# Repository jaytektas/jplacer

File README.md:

# jplacer

Pick-and-place machine control, built on JFramework.

## Building

Needs the JFramework SDK installed at `$HOME/jframework-sdk`, plus CMake, Ninja and OpenSSL.

    cmake -S . -B build -G Ninja -DCMAKE_PREFIX_PATH=$HOME/jframework-sdk
    cmake --build build
    ./build/jplacer

## Releases

Linux releases are AppImages that update themselves: jplacer checks for a newer release when it opens
and from Help > Check For Updates…. Edit > Preferences turns the startup check off and on, and opts in
to beta versions.

## License

GPL-3.0-or-later. See [LICENSE](LICENSE).

## Credits

jplacer follows [OpenPnP](https://openpnp.org) and carries some of it (its icons, translations, default
configuration, illustrations and BlindsFeeder models), under OpenPnP's GPL-3.0-or-later: Copyright (C) Jason von
Nieda and the OpenPnP contributors. jplacer is a separate project, not made or endorsed by OpenPnP.
[NOTICE.md](NOTICE.md) says what comes from where, and the licences of what is built in.

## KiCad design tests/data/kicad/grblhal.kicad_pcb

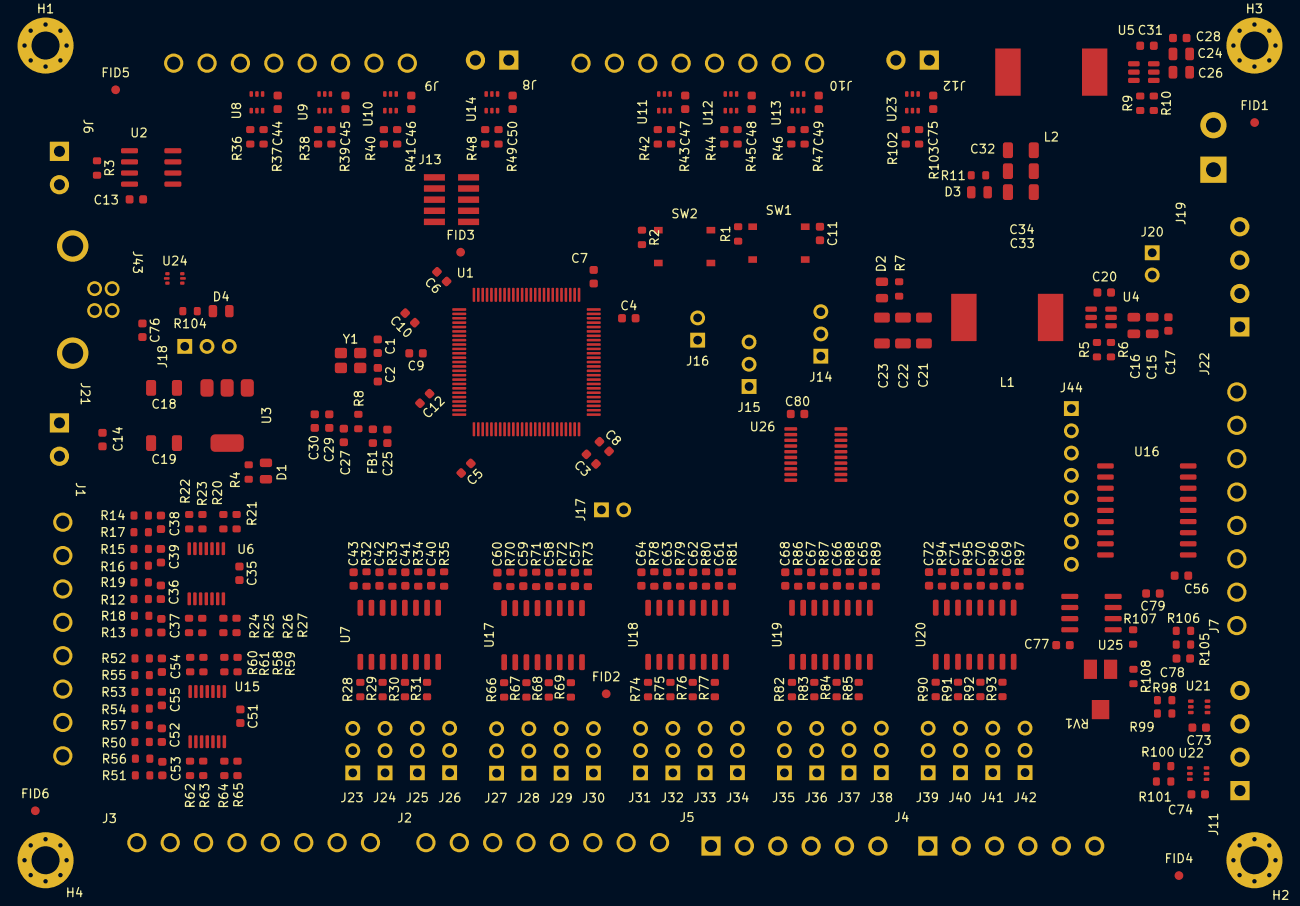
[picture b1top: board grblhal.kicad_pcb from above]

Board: 4 copper layers, 279 parts (0 on the bottom side), 83 nets, no tracks yet.

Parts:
C1, C2: 10pF; C_0603_1608Metric
C3, C4: 2.2u; C_0603_1608Metric
C5, C6, C7, C8, C9, C10, C11, C12, C13, C14, C17, C20, C27, C28, C30, C31, C35, C36, C37, C38, C39, C40, C41, C42, C43, C44, C45, C46, C47, C48, C49, C50, C51, C52, C53, C54, C55, C57, C58, C59, C60, C61, C62, C63, C64, C65, C66, C67, C68, C69, C70, C71, C72, C73, C74, C75, C76, C77, C79, C80: 100nF; C_0603_1608Metric
C15, C16, C24, C26: 4.7uF; C_0805_2012Metric
C18, C19, C21, C22, C23, C32, C33, C34: 22uF; C_1206_3216Metric
C25, C29, C56, C78: 1uF; C_0603_1608Metric
D1, D2, D3, D4: LED; LED_0805_2012Metric
FB1: 380mΩ ±25% 600Ω@100MHz 0603 Ferrite Beads ROHS; L_0603_1608Metric
FID1, FID2, FID3, FID4, FID5, FID6: Fiducial; Fiducial_1mm_Mask2mm
H1, H2, H3, H4: MountingHole_Pad; MountingHole_3.2mm_M3_Pad_Via
J1, J2, J3, J7, J9, J10: Screw_Terminal_01x08; CONN-TH_8P-P3.81_WJ15EDGRC-3.81-8P
J4, J5: Screw_Terminal_01x06; CONN-TH_WJ15EDGRC-3.81-6P
J6, J8, J12, J21: Screw_Terminal_01x02; CONN-TH_2P-P3.81_WJ15EDGRC-3.81-2P
J11, J22: Screw_Terminal_01x04x3; CONN-TH_WJ15EDGRC-3.81-4P
J13: Conn_ARM_JTAG_SWD_10; PinHeader_2x05_P1.27mm_Vertical_SMD
J14, J15, J18, J23, J24, J25, J26, J27, J28, J29, J30, J31, J32, J33, J34, J35, J36, J37, J38, J39, J40, J41, J42: Conn_01x03_Pin; PinHeader_1x03_P2.54mm_Vertical
J16, J17, J20: Conn_01x02_Pin; PinHeader_1x02_P2.54mm_Vertical
J19: Screw_Terminal_01x02x5; CONN-TH_2P-P5.08_WJ2EDGRC-5.08-2P
J43: USB_B; USB-B_TH_BF90
J44: Conn_01x08_Pin; PinHeader_1x08_P2.54mm_Vertical
L1: 12uH; L_12x12mm_H8mm
L2: 6.8uH; L_12x12mm_H8mm
R1, R2, R16, R17, R18, R19, R21, R23, R25, R27, R36, R37, R38, R39, R40, R41, R42, R43, R44, R45, R46, R47, R48, R49, R54, R55, R56, R57, R59, R61, R63, R65, R98, R99, R100, R101, R102, R103, R105, R106, R107, R108: 10K; R_0603_1608Metric
R3: 120; R_0603_1608Metric
R4: 680; R_0603_1608Metric
R5, R9: 100K; R_0603_1608Metric
R6: 5.23K; R_0603_1608Metric
R7: 2.4K; R_0603_1608Metric
R8: 47; R_0603_1608Metric
R10: 13.7K; R_0603_1608Metric
R11, R28, R29, R30, R31, R32, R33, R34, R35, R66, R67, R68, R69, R70, R71, R72, R73, R74, R75, R76, R77, R78, R79, R80, R81, R82, R83, R84, R85, R86, R87, R88, R89, R90, R91, R92, R93, R94, R95, R96, R97, R104: 1K; R_0603_1608Metric
R12, R13, R14, R15, R50, R51, R52, R53: 470K; R_0603_1608Metric
R20, R22, R24, R26, R58, R60, R62, R64: 5.6K; R_0603_1608Metric
RV1: 2K; RES-ADJ-SMD_G43AT
SW1, SW2: SW_Push; SW_Push_1P1T_XKB_TS-1187A
U1: STM32F407VETx; LQFP-100_14x14mm_P0.5mm
U2: MAX3078E; SOIC-8_3.9x4.9mm_P1.27mm
U3: AMS1117-3.3; SOT-223-3_TabPin2
U4, U5: LMR51430; SOT-23-6
U6, U15: MCP6004; TSSOP-14_4.4x5mm_P0.65mm
U7, U17, U18, U19, U20: ELQ3H4(TA)-G; SOP-16_4.4x10.4mm_P1.27mm
U8, U9, U10, U11, U12, U13, U14, U21, U22, U23: 74HC2G34; SOT-363_SC-70-6
U16: ULN2803A; SOP-18_7.495x11.515mm_P1.27mm
U24: USBLC6-2P6; SOT-666
U25: LM358; SOIC-8_3.9x4.9mm_P1.27mm
U26: SN74LVC245APW; TSSOP-20_4.4x6.5mm_P0.65mm
Y1: 8Mhz; Crystal_SMD_3225-4Pin_3.2x2.5mm

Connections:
unnamed: C25.2, C27.2, C29.2, C30.2
unnamed: C78.1, R105.2, R106.1
unnamed: D1.1 (K), R4.1
unnamed: D2.1 (K), R7.1
unnamed: D3.1 (K), R11.1
unnamed: D4.1 (K), R104.1
unnamed: J44.1, U16.1 (I1), U26.18 (B1)
unnamed: J44.2, U16.2 (I2), U26.17 (B2)
unnamed: J44.3, U16.3 (I3), U26.16 (B3)
unnamed: J44.4, U16.4 (I4), U26.15 (B4)
unnamed: J44.5, U16.5 (I5), U26.14 (B5)
unnamed: J44.6, U16.6 (I6), U26.13 (B6)
unnamed: J44.7, U16.7 (I7), U26.12 (B7)
unnamed: J44.8, U16.8 (I8), U26.11 (B8)
unnamed: R107.2, RV1.1
unnamed: R108.1, RV1.3
unnamed: C3.1, U1.49 (VCAP_1)
unnamed: C4.1, U1.73 (VCAP_2)
unnamed: C20.1, U4.6 (CB)
unnamed: R5.2, R6.1, U4.4 (FB)
unnamed: C20.2, L1.1, U4.2 (SW)
unnamed: C31.1, U5.6 (CB)
unnamed: R9.2, R10.1, U5.4 (FB)
unnamed: C31.2, L2.1, U5.2 (SW)
unnamed: C39.1, R16.2, U6.3 (+)
unnamed: R20.1, U6.1, U6.2 (-)
unnamed: C38.1, R17.2, U6.5 (+)
unnamed: R22.1, U6.6 (-), U6.7
unnamed: C37.1, R18.2, U6.10 (+)
unnamed: R24.1, U6.8, U6.9 (-)
unnamed: C36.1, R19.2, U6.12 (+)
unnamed: R26.1, U6.13 (-), U6.14
unnamed: R28.2, U7.1 (A-C1)
unnamed: R29.2, U7.3 (A-C2)
unnamed: R30.2, U7.5 (A-C3)
unnamed: R31.2, U7.7 (A-C4)
unnamed: C41.1, R34.1, U7.12 (CO2)
unnamed: C40.1, R35.1, U7.10 (COL1)
unnamed: C42.1, R33.1, U7.14 (COL3)
unnamed: C43.1, R32.1, U7.16 (COL4)
unnamed: C55.1, R54.2, U15.3 (+)
unnamed: R58.1, U15.1, U15.2 (-)
unnamed: C54.1, R55.2, U15.5 (+)
unnamed: R60.1, U15.6 (-), U15.7
unnamed: C53.1, R56.2, U15.10 (+)
unnamed: R62.1, U15.8, U15.9 (-)
unnamed: C52.1, R57.2, U15.12 (+)
unnamed: R64.1, U15.13 (-), U15.14
unnamed: R66.2, U17.1 (A-C1)
unnamed: R67.2, U17.3 (A-C2)
unnamed: R68.2, U17.5 (A-C3)
unnamed: R69.2, U17.7 (A-C4)
unnamed: C58.1, R72.1, U17.12 (CO2)
unnamed: C57.1, R73.1, U17.10 (COL1)
unnamed: C59.1, R71.1, U17.14 (COL3)
unnamed: C60.1, R70.1, U17.16 (COL4)
unnamed: R74.2, U18.1 (A-C1)
unnamed: R75.2, U18.3 (A-C2)
unnamed: R76.2, U18.5 (A-C3)
unnamed: R77.2, U18.7 (A-C4)
unnamed: C62.1, R80.1, U18.12 (CO2)
unnamed: C61.1, R81.1, U18.10 (COL1)
unnamed: C63.1, R79.1, U18.14 (COL3)
unnamed: C64.1, R78.1, U18.16 (COL4)
unnamed: R82.2, U19.1 (A-C1)
unnamed: R83.2, U19.3 (A-C2)
unnamed: R84.2, U19.5 (A-C3)
unnamed: R85.2, U19.7 (A-C4)
unnamed: C66.1, R88.1, U19.12 (CO2)
unnamed: C65.1, R89.1, U19.10 (COL1)
unnamed: C67.1, R87.1, U19.14 (COL3)
unnamed: C68.1, R86.1, U19.16 (COL4)
unnamed: R90.2, U20.1 (A-C1)
unnamed: R91.2, U20.3 (A-C2)
unnamed: R92.2, U20.5 (A-C3)
unnamed: R93.2, U20.7 (A-C4)
unnamed: C70.1, R96.1, U20.12 (CO2)
unnamed: C69.1, R97.1, U20.10 (COL1)
unnamed: C71.1, R95.1, U20.14 (COL3)
unnamed: C72.1, R94.1, U20.16 (COL4)
unnamed: C79.1, R106.2, U25.3 (+)
unnamed: RV1.2, U25.2 (-)
unnamed: U25.6 (-), U25.7
